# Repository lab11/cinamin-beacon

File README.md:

Cinamin Beacon
==============

This project is dedicated to the development of a sub-cubic-centimeter, 
solar powered, bluetooth low energy beacon.

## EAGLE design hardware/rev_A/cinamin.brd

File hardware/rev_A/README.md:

This is the first pass of the cinamin actual cinamin board.

Mousbites break the board off from the programming header and the
testpoints necessary for programming the OTP memory

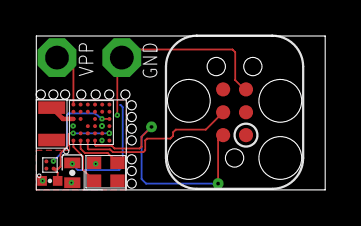
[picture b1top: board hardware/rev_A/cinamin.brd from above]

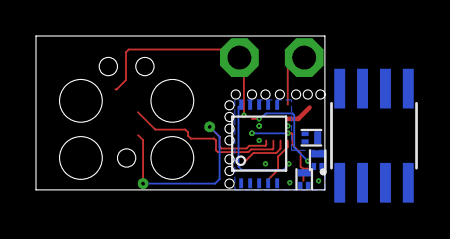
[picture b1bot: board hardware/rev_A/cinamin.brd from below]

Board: 2 copper layers, 16.1 x 8.6 mm, 14 parts (5 on the bottom side), 12 nets.

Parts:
A1: AH212M
C1: 47uF; 0603_CAP_SMALL
C6: 1uF; 0402_CAP
D1: CPC1822; SOIC-8
PROG1: TC2030-JLINK-L; TC2030-IDC
Q1, Q2: XFDFN-3
Q3: MOSFET-NCHANNELXFDN-3; XFDFN-3
TP1, TP2: TPSPAD1-13; P1-13
U1: AP4400_3.4_2.3; TSOP-10
U$3: DA14581-BGA; WLCSP-34
U$4: LD391151.4V; FLIP_CHIP-4
X1: 16Mhz; TXC-8Y

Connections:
GND: C1.NEG, C6.2, D1.5, PROG1.5, Q3.S, TP2.TP, U1.5, U$3.A3, U$3.E1, U$3.E3, U$4.A1, X1.2, X1.4
unnamed: TP1.TP, U$3.A6
unnamed: Q1.G, Q3.G, U1.6
unnamed: C1.POS, D1.8, Q1.S, Q2.S, U1.10
unnamed: Q1.D, Q2.G, Q3.D
unnamed: U$3.B1, X1.3
unnamed: U$3.A1, X1.1
unnamed: A1.P1, U$3.A4
OUT: C6.1, U$3.A2, U$3.F2, U$4.B1
SWDIO: PROG1.2, U$3.D1
SW_CLK: PROG1.4, U$3.C1
VCC: Q2.D, U$3.E4, U$3.F4, U$4.A2, U$4.B2

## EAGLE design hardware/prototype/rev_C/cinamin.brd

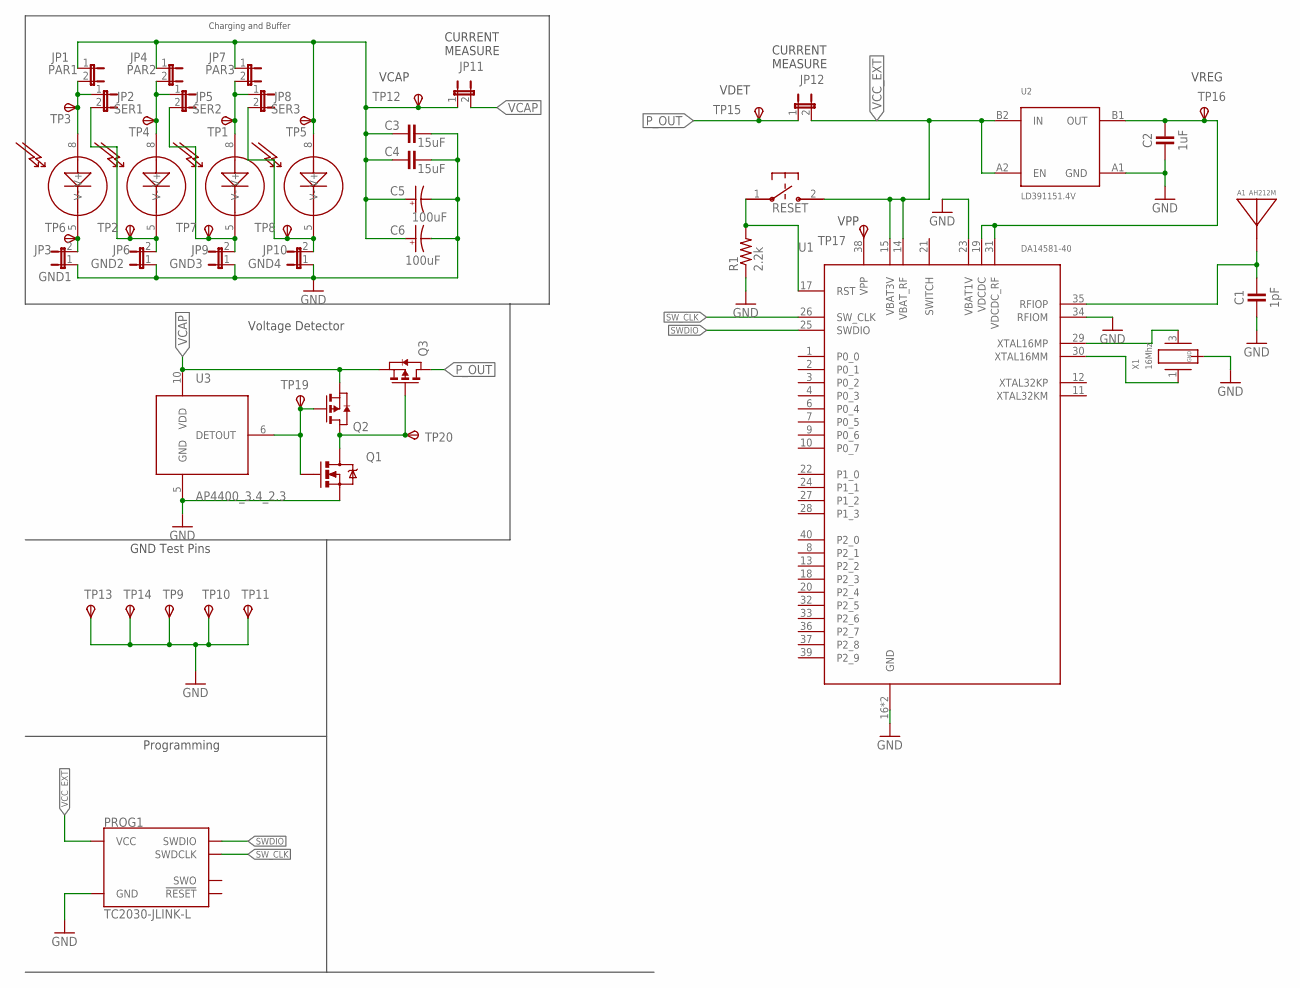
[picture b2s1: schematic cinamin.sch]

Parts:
A1: AH212M
C1: 1pF; 0402_CAP
C2: 1uF; 0402_CAP
C3, C4: 15uF; 0402_CAP
C5, C6: 100uF; CAP0603
D1, D2, D3, D4: CPC1822; SOIC-8
JP1: PAR1; 1X02
JP2: SER1; 1X02
JP3: GND1; 1X02
JP4: PAR2; 1X02
JP5: SER2; 1X02
JP6: GND2; 1X02
JP7: PAR3; 1X02
JP8: SER3; 1X02
JP9: GND3; 1X02
JP10: GND4; 1X02
JP11: CURRENT_MEASURE1; 1X02
JP12: CURRENT_MEASURE2; 1X02
PROG1: TC2030-JLINK-L; TC2030-IDC
Q1: MOSFET-NCHANNELXFDN-3; XFDFN-3
Q2, Q3: MOSFET-PCHANNEL; XFDFN-3
R1: 2.2k; 0402_RES
RESET: B3U-1000P
TP1: D3H; P1-13
TP2: D2L; P1-13
TP3: D1H; P1-13
TP4: D2H; P1-13
TP5: D4H; P1-13
TP6: D1L; P1-13
TP7: D3L; P1-13
TP8: D4L; P1-13
TP9, TP10, TP11, TP13, TP14: GND; P1-13
TP12, TP19, TP20: VCAP; P1-13
TP15: VDET; P1-13
TP16: VREG; P1-13
TP17: VPP; P1-13
U1: DA14581-40; QFN-40-5MM
U2: LD391151.4V; FLIP_CHIP-4
U3: AP4400_3.4_2.3; TSOP-10
X1: 16Mhz; TXC-8Y

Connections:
DET_OUT: Q1.G, Q2.G, TP19.TP, U3.6 (DETOUT)
GND: C1.2, C2.2, C3.2, C4.2, C5.NEG (ANODE), C6.NEG (ANODE), JP3.1, JP6.1, JP9.1, JP10.1, PROG1.5 (GND), Q1.S, R1.1, TP9.TP, TP10.TP, TP11.TP, TP13.TP, TP14.TP, U1.16 (GND), U1.23 (VBAT1V), U1.34 (RFIOM), U1.PAD (GND), U2.A1 (GND), U3.5 (GND), X1.2 (GND), X1.4 (GND)
JP10: D4.5 (V-), JP8.2, JP10.2, TP8.TP
unnamed: C3.1, C4.1, C5.POS (CATHODE), C6.POS (CATHODE), D4.8 (V+), JP1.1, JP4.1, JP7.1, JP11.1, TP5.TP, TP12.TP
unnamed: TP17.TP, U1.38 (VPP)
unnamed: C2.1, TP16.TP, U1.19 (VDCDC), U1.31 (VDCDC_RF), U2.B1 (OUT)
unnamed: Q1.D, Q2.D, Q3.G, TP20.TP
unnamed: U1.29 (XTAL16MP), X1.3 (2)
unnamed: U1.30 (XTAL16MM), X1.1
unnamed: A1.P1, C1.1, U1.35 (RFIOP)
unnamed: R1.2, RESET.1, U1.17 (RST)
unnamed: D1.5 (V-), JP3.2, TP6.TP
unnamed: D2.5 (V-), JP2.2, JP6.2, TP2.TP
unnamed: D3.5 (V-), JP5.2, JP9.2, TP7.TP
unnamed: D1.8 (V+), JP1.2, JP2.1, TP3.TP
unnamed: D2.8 (V+), JP4.2, JP5.1, TP4.TP
unnamed: D3.8 (V+), JP7.2, JP8.1, TP1.TP
P_OUT: JP12.1, Q3.D, TP15.TP
SWDIO: PROG1.2 (SWDIO), U1.25 (SWDIO)
SW_CLK: PROG1.4 (SWDCLK), U1.26 (SW_CLK)
VCAP: JP11.2, Q2.S, Q3.S, U3.10 (VDD)
VCC_EXT: JP12.2, PROG1.1 (VCC), RESET.2, U1.14 (VBAT_RF), U1.15 (VBAT3V), U2.A2 (EN), U2.B2 (IN)

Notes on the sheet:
Charging and Buffer
Programming
GND Test Pins
Voltage Detector
VCAP
VDET
CURRENT MEASURE
VREG
VPP

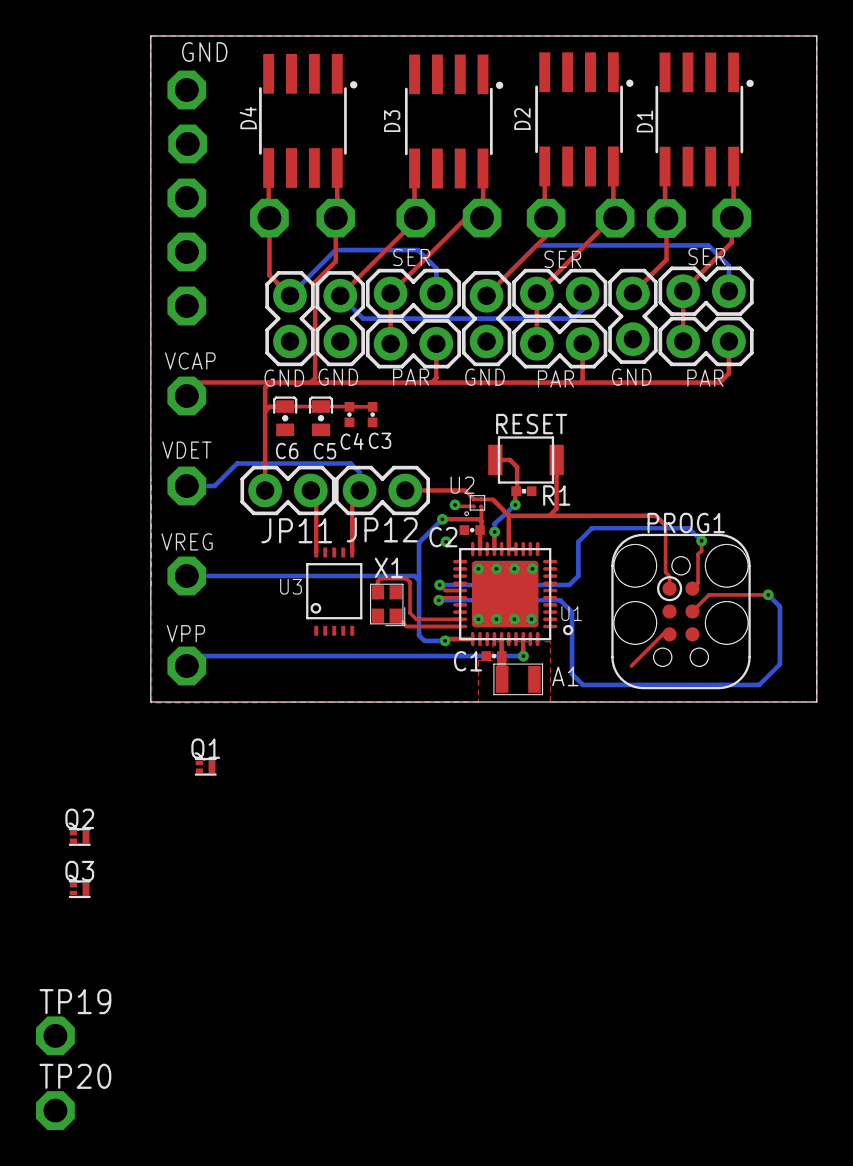
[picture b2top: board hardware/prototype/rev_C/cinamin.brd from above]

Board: 2 copper layers, 37.0 x 37.0 mm, 52 parts (0 on the bottom side), 22 nets.

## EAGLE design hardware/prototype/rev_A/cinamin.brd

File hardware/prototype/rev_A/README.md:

This board is for prototyping in a less compact form factor

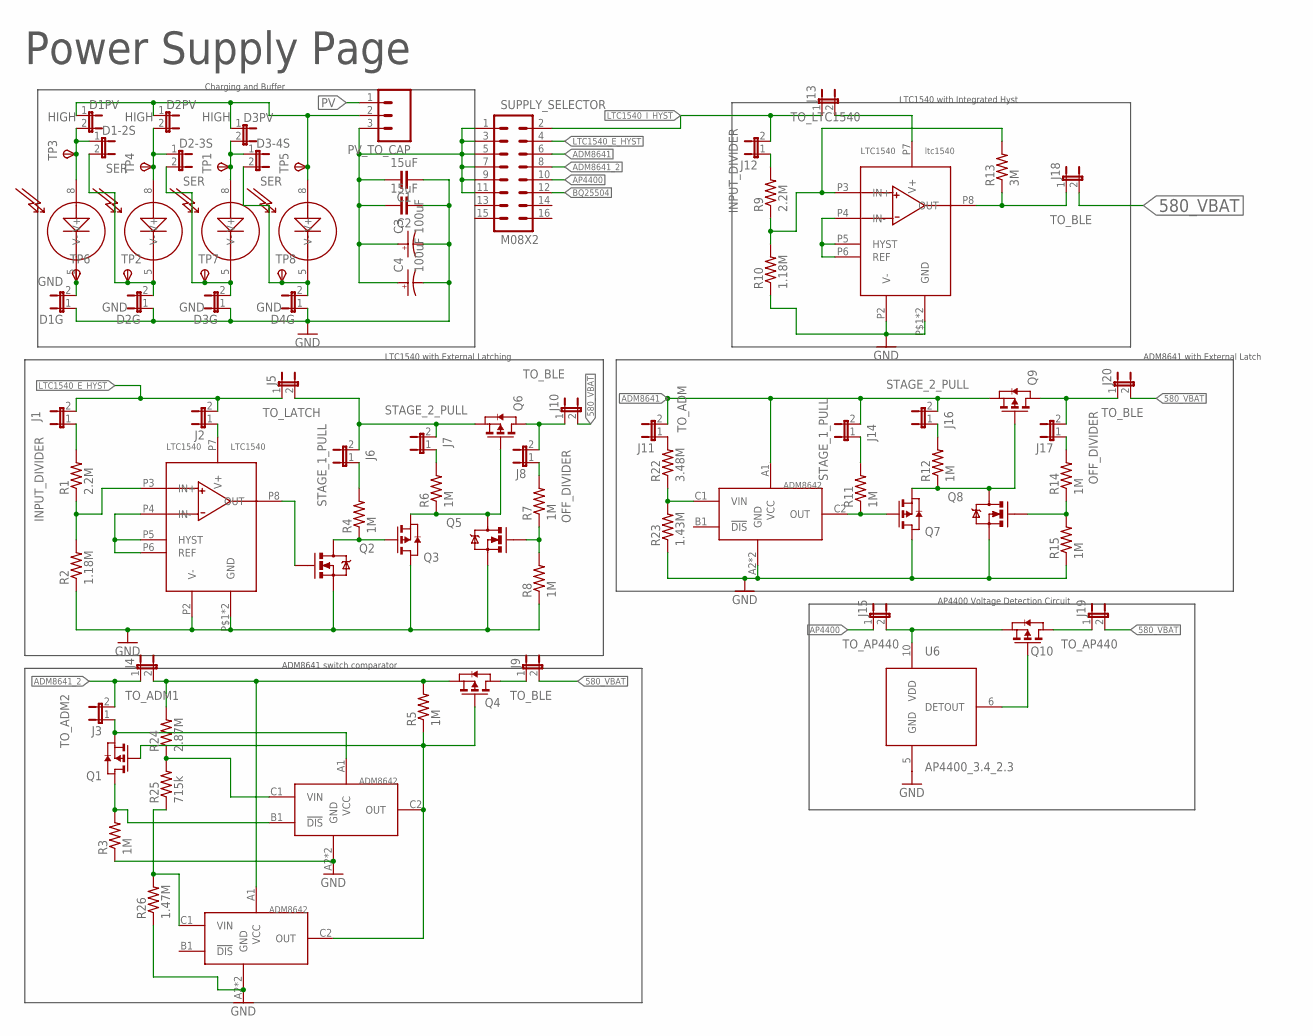
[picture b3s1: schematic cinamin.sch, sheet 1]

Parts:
C1, C2: 15uF; 0402_CAP
C3, C4: 100uF; CAP0603
D1, D2, D3, D4: CPC1822; SOIC-8
D1-2S, D2-3S, D3-4S: SER; 1X02
D1G, D2G, D3G, D4G: GND; 1X02
D1PV, D2PV, D3PV: HIGH; 1X02
J1, J12: INPUT_DIVIDER; 1X02
J2: JUMPER-2PTH; 1X02
J3: TO_ADM2; 1X02
J4: TO_ADM1; 1X02
J5: TO_LATCH; 1X02
J6, J14: STAGE_1_PULL; 1X02
J7, J16: STAGE_2_PULL; 1X02
J8, J17: OFF_DIVIDER; 1X02
J9, J10, J18, J20: TO_BLE; 1X02
J11: TO_ADM; 1X02
J13: TO_LTC1540; 1X02
J15, J19: TO_AP440; 1X02
PV_TO_CAP: M03PTH; 1X03
Q1, Q3, Q4, Q6, Q7, Q9, Q10: MOSFET-PCHANNEL; XFDFN-3
Q2, Q5, Q8: MOSFET-NCHANNELXFDN-3; XFDFN-3
R1, R9: 2.2M; 0402_RES
R2, R10: 1.18M; 0402_RES
R3, R4, R5, R6, R7, R8, R11, R12, R14, R15: 1M; 0402_RES
R13: 3M; 0402_RES
R22: 3.48M; 0402_RES
R23: 1.43M; 0402_RES
R24: 2.87M; 0402_RES
R25: 715k; 0402_RES
R26: 1.47M; 0402_RES
SUPPLY_SELECTOR: M08X2; 2X8
TP1, TP2, TP3, TP4, TP5, TP6, TP7, TP8: TPSPAD1-13; P1-13
U1: LTC1540; DFN-8
U2, U3, U4: ADM8642; WLCSP-6
U5: ltc1540; DFN-8
U6: AP4400_3.4_2.3; TSOP-10

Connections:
580_VBAT: J9.2, J10.2, J18.2, J19.2, J20.2; also elsewhere on the board
ADM8641: J11.2, J14.2, J16.2, Q9.S, SUPPLY_SELECTOR.6, U4.A1 (VCC)
ADM8641_2: J3.2, J4.1, SUPPLY_SELECTOR.8
AP4400: J15.1, SUPPLY_SELECTOR.10
BQ25504: SUPPLY_SELECTOR.12; also elsewhere on the board
GND: C1.2, C2.2, C3.NEG (ANODE), C4.NEG (ANODE), D1G.1, D2G.1, D3G.1, D4G.1, Q2.S, Q3.D, Q5.S, Q7.D, Q8.S, R2.1, R3.1, R8.1, R10.1, R15.1, R23.1, R26.1, U1.P1 (GND), U1.P2 (V-), U1.P$1 (GND), U2.A2 (GND), U2.B2 (GND), U3.A2 (GND), U3.B2 (GND), U4.A2 (GND), U4.B2 (GND), U5.P1 (GND), U5.P2 (V-), U5.P$1 (GND), U6.5 (GND); also elsewhere on the board
HIGH: J19.1, Q10.D
LTC1540_E_HYST: J1.2, J2.2, J5.1, SUPPLY_SELECTOR.4
LTC1540_I_HYST: J12.2, J13.1, SUPPLY_SELECTOR.2
unnamed: C1.1, C2.1, C3.POS (CATHODE), C4.POS (CATHODE), PV_TO_CAP.3, SUPPLY_SELECTOR.1, SUPPLY_SELECTOR.3, SUPPLY_SELECTOR.5, SUPPLY_SELECTOR.7, SUPPLY_SELECTOR.9, SUPPLY_SELECTOR.11
unnamed: U1.P4 (IN-), U1.P5 (HYST), U1.P6 (REF)
unnamed: R9.1, R10.2, R13.2, U5.P3 (IN+)
unnamed: U5.P4 (IN-), U5.P5 (HYST), U5.P6 (REF)
unnamed: Q2.G, U1.P8 (OUT)
unnamed: J11.1, R22.2
unnamed: R1.1, R2.2, U1.P3 (IN+)
unnamed: Q2.D, Q3.G, R4.1
unnamed: J1.1, R1.2
unnamed: Q3.S, Q5.D, Q6.G, R6.1
unnamed: J2.1, U1.P7 (V+)
unnamed: J6.1, R4.2
unnamed: J7.1, R6.2
unnamed: Q5.G, R7.1, R8.2
unnamed: J8.2, J10.1, Q6.D
unnamed: J5.2, J6.2, J7.2, Q6.S
unnamed: J8.1, R7.2
unnamed: J12.1, R9.2
unnamed: J13.2, U5.P7 (V+)
unnamed: Q7.G, R11.1, U4.C2 (OUT)
unnamed: Q7.S, Q8.D, Q9.G, R12.1
unnamed: Q8.G, R14.1, R15.2
unnamed: J17.2, J20.1, Q9.D
unnamed: J14.1, R11.2
unnamed: J16.1, R12.2
unnamed: R24.1, R25.2, U3.C1 (VIN)
unnamed: J17.1, R14.2
unnamed: Q10.G, U6.6 (DETOUT)
unnamed: J9.1, Q4.D
unnamed: Q1.D, R3.2, U3.B1 (!DIS)
unnamed: J3.1, Q1.S, U3.A1 (VCC)
unnamed: Q1.G, Q4.G, R5.1, U2.C2 (OUT), U3.C2 (OUT)
unnamed: J4.2, Q4.S, R5.2, R24.2, U2.A1 (VCC)
unnamed: D3-4S.2, D4.5 (V-), D4G.2, TP8.TP
unnamed: R22.1, R23.2, U4.C1 (VIN)
unnamed: R25.1, R26.2, U2.C1 (VIN)
unnamed: D1.5 (V-), D1G.2, TP6.TP
unnamed: D1-2S.2, D2.5 (V-), D2G.2, TP2.TP
unnamed: D2-3S.2, D3.5 (V-), D3G.2, TP7.TP
unnamed: D1.8 (V+), D1-2S.1, D1PV.2, TP3.TP
unnamed: D1PV.1, D2PV.1, D3PV.1, D4.8 (V+), PV_TO_CAP.2, TP5.TP
unnamed: D2.8 (V+), D2-3S.1, D2PV.2, TP4.TP
unnamed: D3.8 (V+), D3-4S.1, D3PV.2, TP1.TP
OUT: J18.1, R13.1, U5.P8 (OUT)
PV: PV_TO_CAP.1; also elsewhere on the board
VDD: J15.2, Q10.S, U6.10 (VDD)

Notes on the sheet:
Power Supply Page
LTC1540 with Integrated Hyst
LTC1540 with External Latching
ADM8641 with External Latch
Charging and Buffer
ADM8641 switch comparator
AP4400 Voltage Detection Circuit

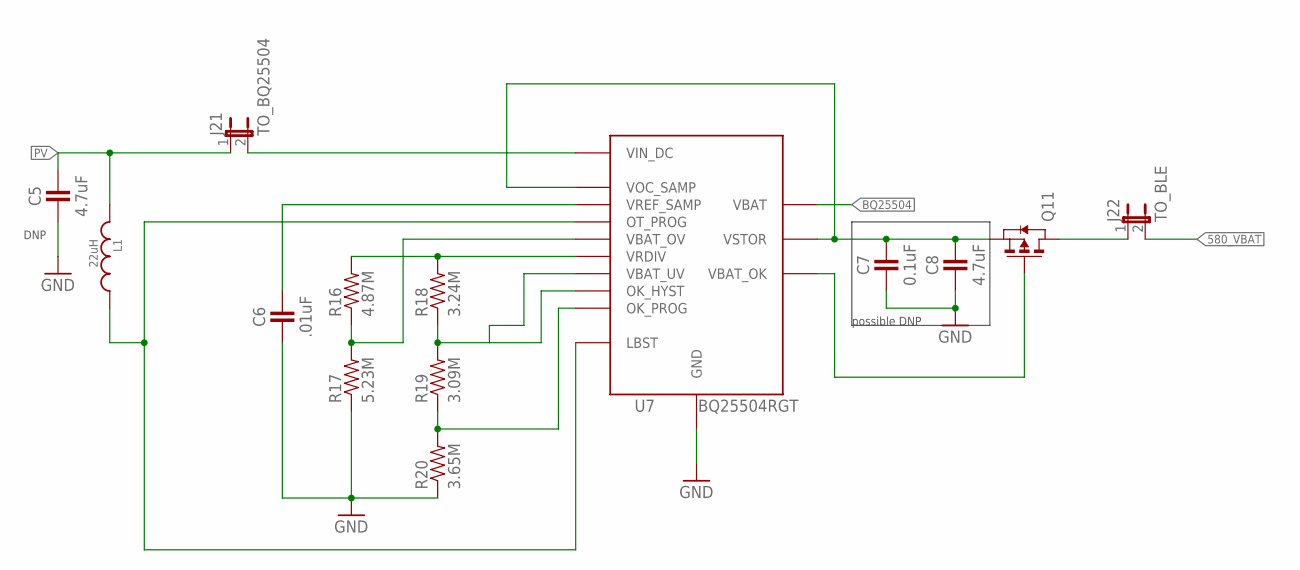
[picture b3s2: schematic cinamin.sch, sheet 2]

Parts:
C5, C8: 4.7uF; 0402_CAP
C6: .01uF; 0402_CAP
C7: 0.1uF; 0402_CAP
J21: TO_BQ25504; 1X02
J22: TO_BLE; 1X02
L1: 22uH; 0603_CAP
Q11: MOSFET-PCHANNEL; XFDFN-3
R16: 4.87M; 0402_RES
R17: 5.23M; 0402_RES
R18: 3.24M; 0402_RES
R19: 3.09M; 0402_RES
R20: 3.65M; 0402_RES
U7: BQ25504RGT; S-PVQFN-N16

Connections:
580_VBAT: J22.2; also elsewhere on the board
BQ25504: U7.14 (VBAT); also elsewhere on the board
GND: C5.2, C6.2, C7.2, C8.2, R17.1, R20.1, U7.1 (GND), U7.12 (GND), U7.13 (GND); also elsewhere on the board
unnamed: L1.1, U7.5 (OT_PROG), U7.16 (LBST)
unnamed: R16.2, R18.2, U7.7 (VRDIV)
unnamed: Q11.G, U7.11 (VBAT_OK)
unnamed: R18.1, R19.2, U7.9 (OK_HYST)
unnamed: R19.1, R20.2, U7.10 (OK_PROG)
unnamed: C6.1, U7.4 (VREF_SAMP)
unnamed: R16.1, R17.2, U7.6 (VBAT_OV)
OUT2: J22.1, Q11.D
PV: C5.1, J21.1, L1.2; also elsewhere on the board
VIN_DC: J21.2, U7.2 (VIN_DC)
VSTOR: C7.1, C8.1, Q11.S, U7.3 (VOC_SAMP), U7.15 (VSTOR)

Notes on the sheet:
possible DNP
DNP

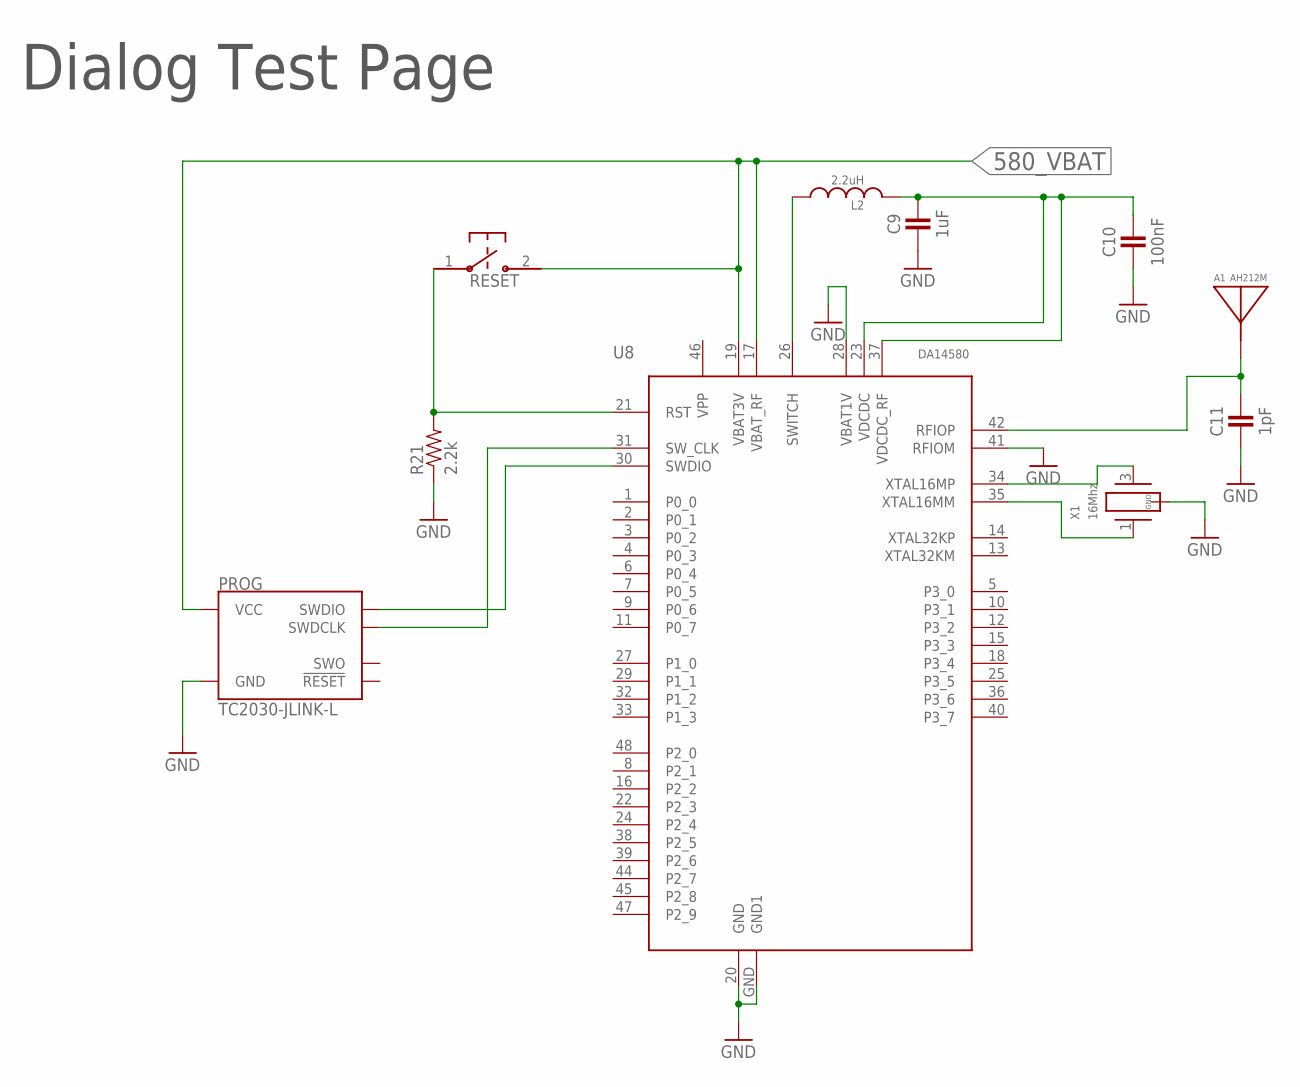
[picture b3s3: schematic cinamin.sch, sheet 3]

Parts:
A1: AH212M
C9: 1uF; 0402_CAP
C10: 100nF; 0402_CAP
C11: 1pF; 0402_CAP
L2: 2.2uH; 0402_CAP
PROG: TC2030-JLINK-L; TC2030-IDC
R21: 2.2k; 0402_RES
RESET: B3U-1000P
U8: DA14580; QFN-48-6MM
X1: 16Mhz; TXC-8Y

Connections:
580_VBAT: PROG.1 (VCC), RESET.2, U8.17 (VBAT_RF), U8.19 (VBAT3V); also elsewhere on the board
GND: C9.2, C10.2, C11.2, PROG.5 (GND), R21.1, U8.20 (GND), U8.28 (VBAT1V), U8.41 (RFIOM), U8.GND (GND1), X1.2 (GND), X1.4 (GND); also elsewhere on the board
unnamed: A1.P1, C11.1, U8.42 (RFIOP)
unnamed: L2.1, U8.26 (SWITCH)
unnamed: C9.1, C10.1, L2.2, U8.23 (VDCDC), U8.37 (VDCDC_RF)
unnamed: U8.34 (XTAL16MP), X1.3 (2)
unnamed: U8.35 (XTAL16MM), X1.1
unnamed: PROG.2 (SWDIO), U8.30 (SWDIO)
unnamed: PROG.4 (SWDCLK), U8.31 (SW_CLK)
unnamed: R21.2, RESET.1, U8.21 (RST)

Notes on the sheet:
Dialog Test Page

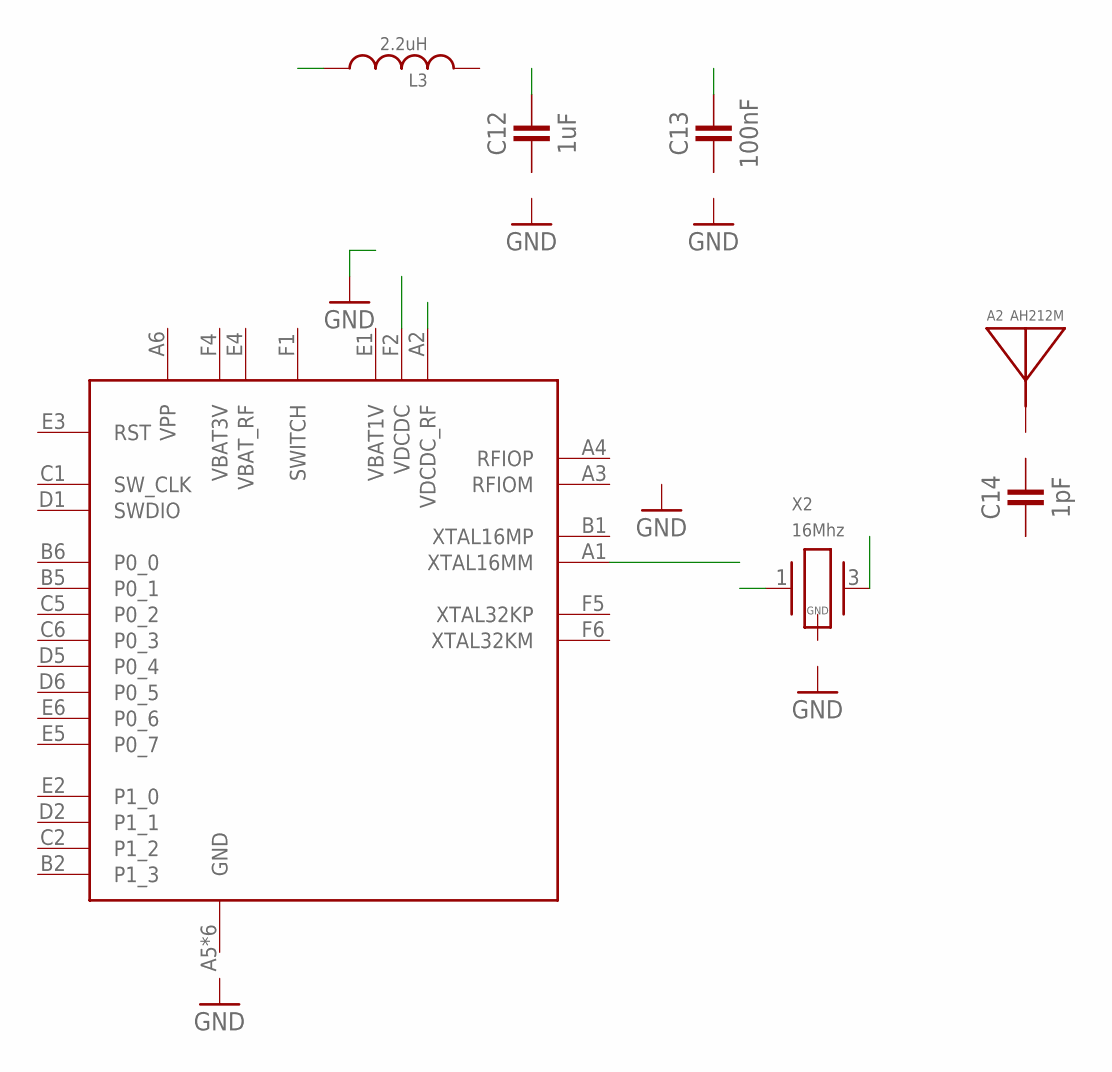
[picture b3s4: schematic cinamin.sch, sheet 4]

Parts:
A2: AH212M; AH212M@1
C12: 1uF; 01005_CAP
C13: 100nF; 01005_CAP
C14: 1pF; 0201_CAP
L3: 2.2uH; 0402_CAP
U9: DA14580-BGA; WLCSP34
X2: 16Mhz; TXC-8Y

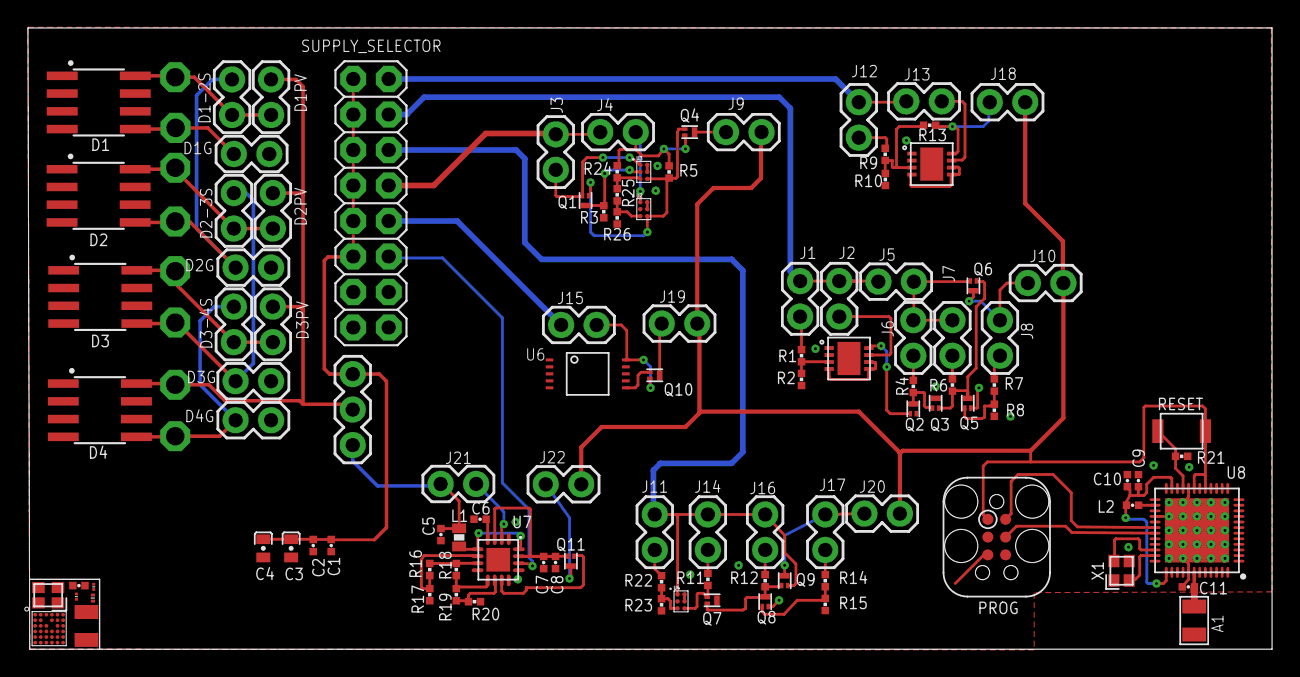
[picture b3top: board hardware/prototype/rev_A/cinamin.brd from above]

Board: 2 copper layers, 89.0 x 44.5 mm, 115 parts (0 on the bottom side), 73 nets.

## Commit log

2015-08-06 power supply schematic first pass and README
2015-08-06 most of the way through layout
2015-08-07 layout and schematic done
2015-08-07 added series parrallel solar jumps
2015-08-10 committing board sent to fab
2015-11-12 add cad mockup
2015-11-17 update cinamin model
2015-11-17 added papers and datasheets
2016-05-25 forked the prototype into 2 revs, schematic started, added gitignore
2016-05-26 added a first pass at routing the actual cinamin board
2016-05-26 prototype board mostly done, clean up board and schematic before ordering tonight
2016-05-27 prototype to production
2016-05-28 cleaned up some traces, changed to 0603 cap
2016-06-06 changed the revand the new prototype to include the transistor switch

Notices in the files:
parts and their libraries:
SparkFun-Aesthetics: Licensing: CC v3.0 Share-Alike You are welcome to use this library for commercial purposes.
